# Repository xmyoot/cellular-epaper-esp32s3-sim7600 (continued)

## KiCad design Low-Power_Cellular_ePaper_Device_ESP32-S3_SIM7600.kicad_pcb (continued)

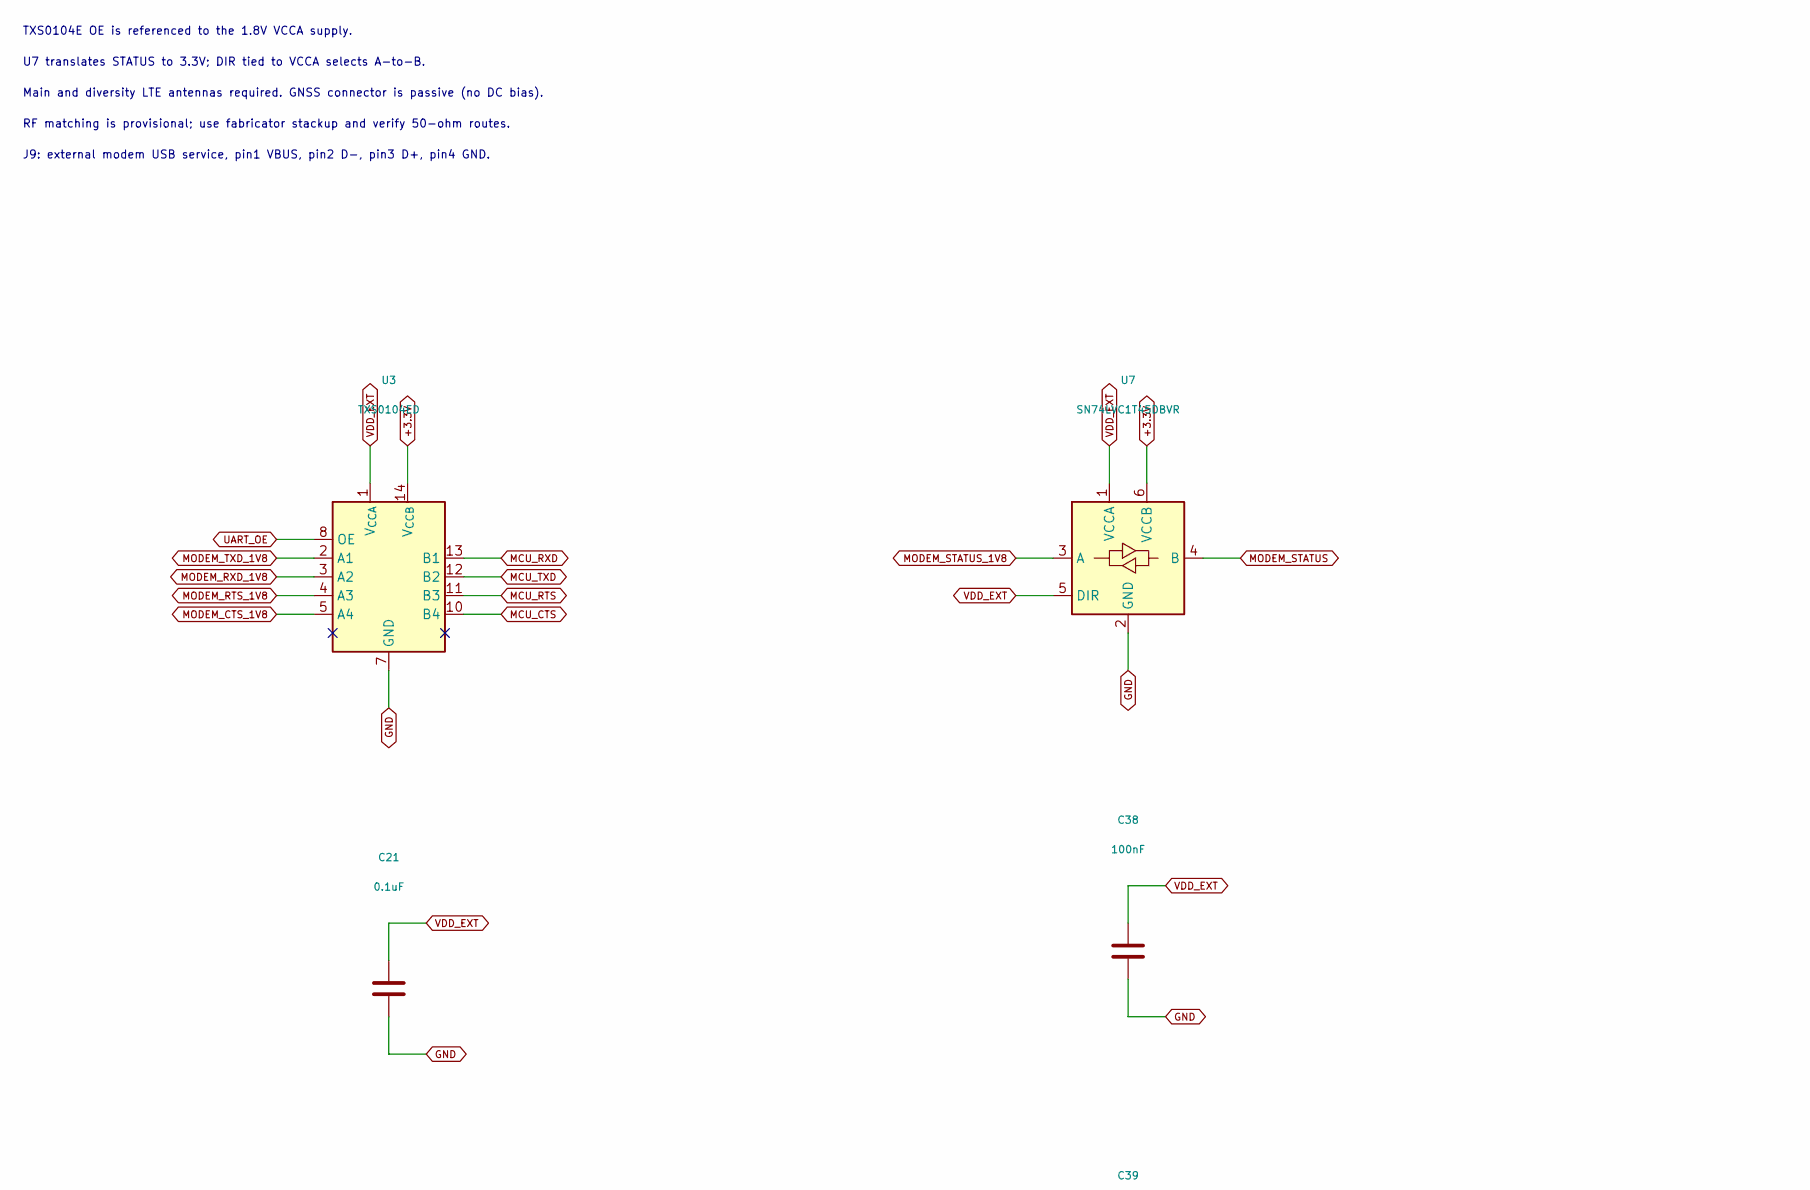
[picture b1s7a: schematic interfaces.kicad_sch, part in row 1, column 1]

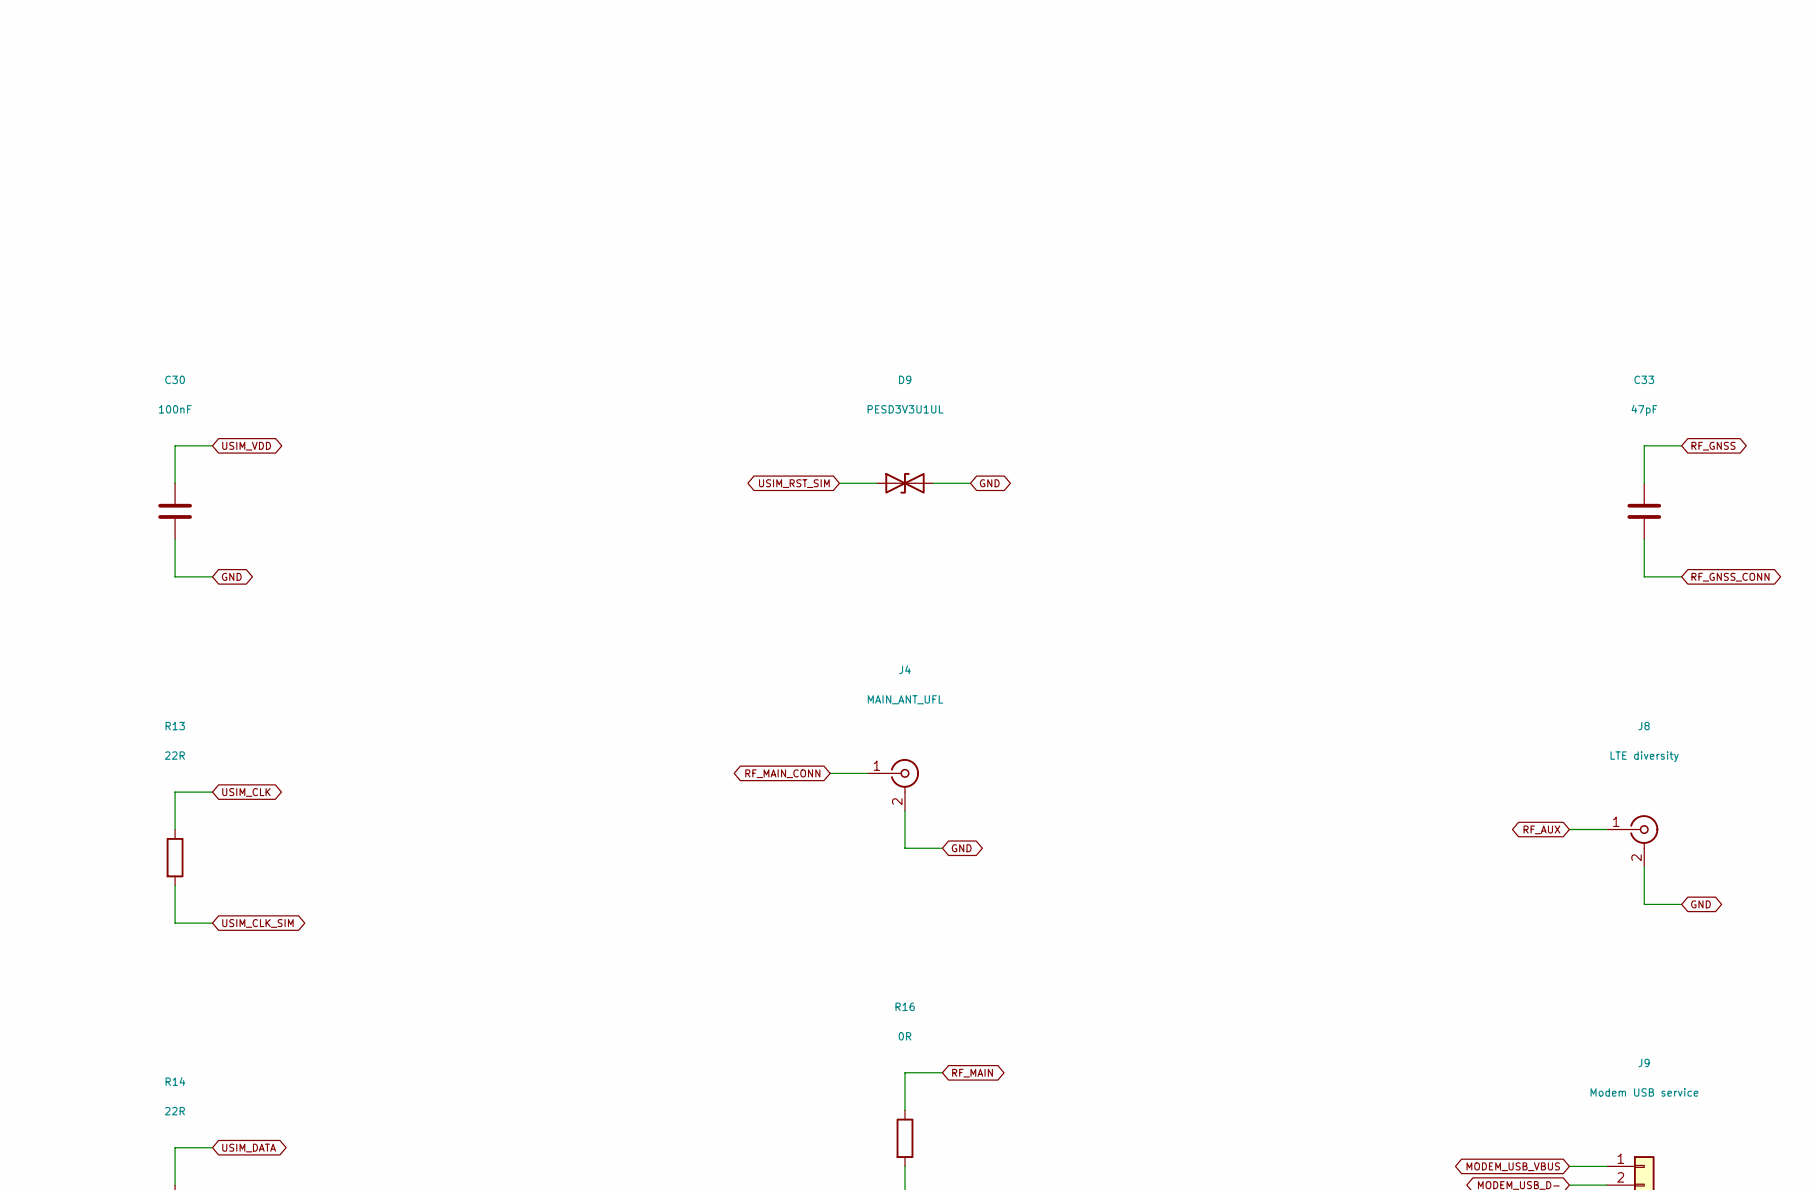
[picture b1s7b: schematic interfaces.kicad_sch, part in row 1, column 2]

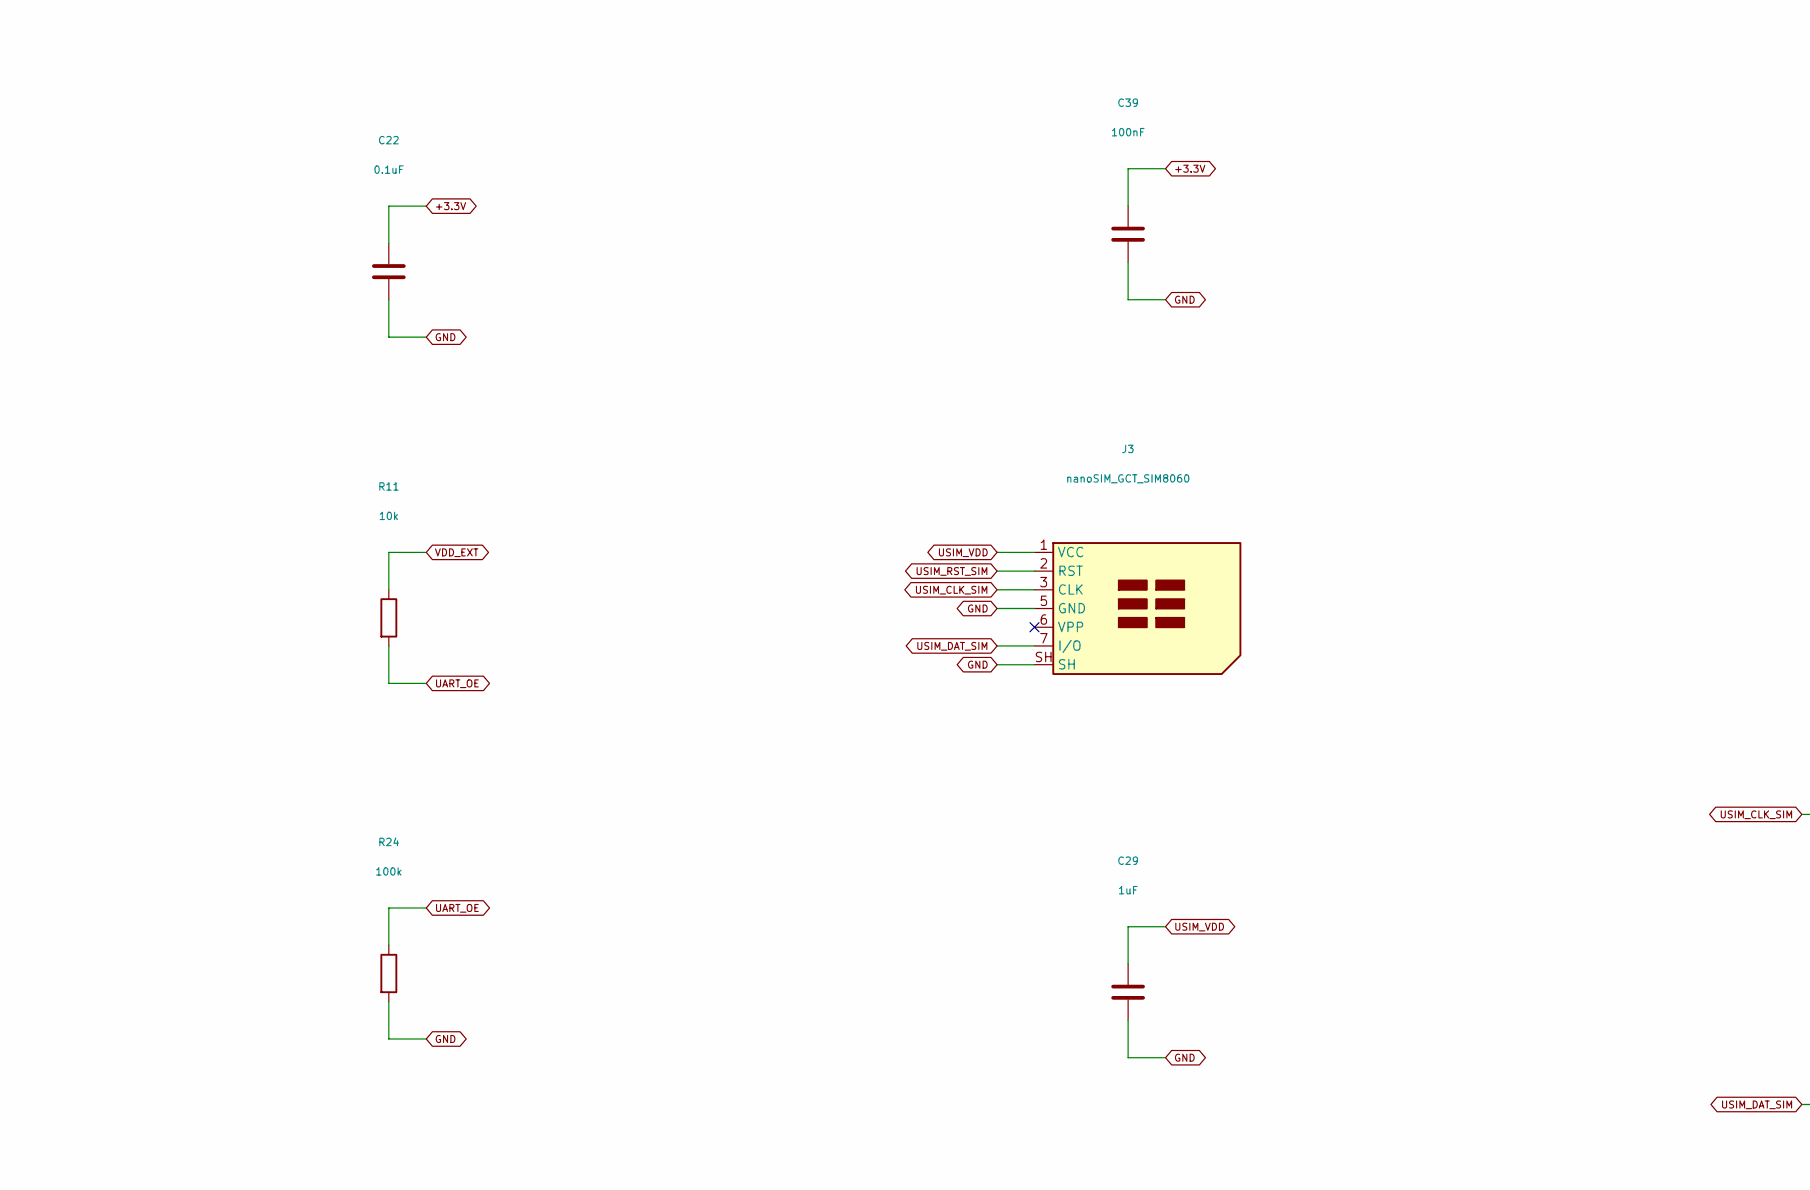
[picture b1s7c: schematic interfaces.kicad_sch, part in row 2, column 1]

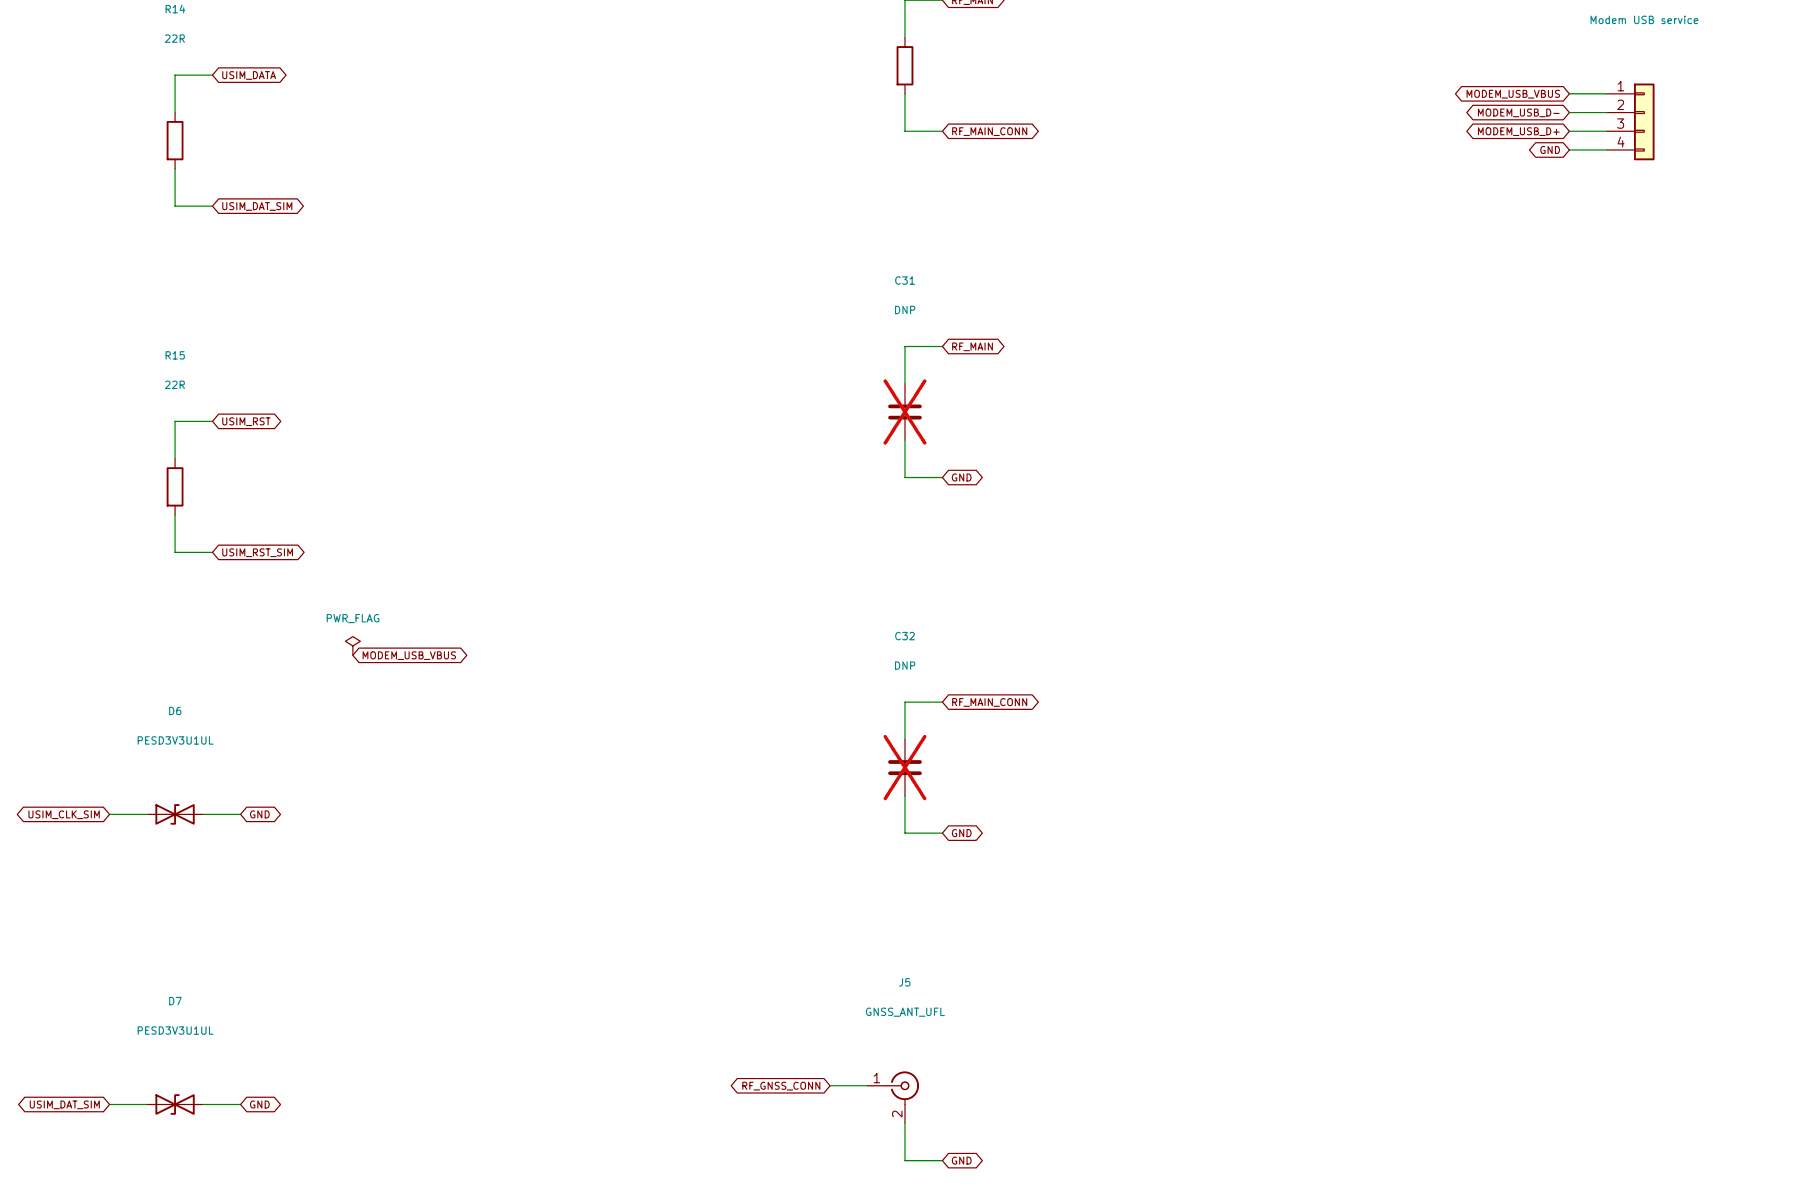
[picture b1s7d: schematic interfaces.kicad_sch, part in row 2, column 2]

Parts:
C21, C22: 0.1uF; C_0402_1005Metric
C29: 1uF; C_0603_1608Metric
C30: 100nF; C_0402_1005Metric
C31, C32: DNP; C_0402_1005Metric; not fitted
C33: 47pF; C_0402_1005Metric
C38, C39: 100nF; C_0603_1608Metric
D6, D9: PESD3V3U1UL; D_SOD-882
D7: PESD3V3U1UL; D_SOD-882_SIM
J3: nanoSIM_GCT_SIM8060; nanoSIM_GCT_SIM8060-6-0-14-00
J4: MAIN_ANT_UFL; U.FL_Hirose_U.FL-R-SMT-1_Vertical
J5: GNSS_ANT_UFL; U.FL_Hirose_U.FL-R-SMT-1_Vertical
J8: LTE diversity; U.FL_Hirose_U.FL-R-SMT-1_Vertical
J9: Modem USB service; PinHeader_1x04_P2.54mm_Vertical
R11: 10k; R_0603_1608Metric
R13, R14, R15: 22R; R_0402_1005Metric
R16: 0R; R_0402_1005Metric
R24: 100k; R_0603_1608Metric
U3: TXS0104ED; SOIC-14_3.9x8.7mm_P1.27mm
U7: SN74LVC1T45DBVR; SOT-23-6

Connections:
+3.3V: C22.1, C39.1, U3.14 (V_{CCB}), U7.6 (VCCB); also elsewhere on the board
GND: C21.2, C22.2, C29.2, C30.2, C31.2, C32.2, C38.2, C39.2, D6.2 (A2), D7.2 (A2), D9.2 (A2), J3.5 (GND), J3.SH, J4.2 (Ext), J5.2 (Ext), J8.2 (Ext), J9.4, R24.2, U3.7 (GND), U7.2 (GND); also elsewhere on the board
MCU_CTS: U3.10 (B4); also elsewhere on the board
MCU_RTS: U3.11 (B3); also elsewhere on the board
MCU_RXD: U3.13 (B1); also elsewhere on the board
MCU_TXD: U3.12 (B2); also elsewhere on the board
MODEM_CTS_1V8: U3.5 (A4); also elsewhere on the board
MODEM_RTS_1V8: U3.4 (A3); also elsewhere on the board
MODEM_RXD_1V8: U3.3 (A2); also elsewhere on the board
MODEM_STATUS: U7.4 (B); also elsewhere on the board
MODEM_STATUS_1V8: U7.3 (A); also elsewhere on the board
MODEM_TXD_1V8: U3.2 (A1); also elsewhere on the board
MODEM_USB_D+: J9.3; also elsewhere on the board
MODEM_USB_D-: J9.2; also elsewhere on the board
MODEM_USB_VBUS: J9.1; also elsewhere on the board
RF_AUX: J8.1 (In); also elsewhere on the board
RF_GNSS: C33.1; also elsewhere on the board
RF_GNSS_CONN: C33.2, J5.1 (In)
RF_MAIN: C31.1, R16.1; also elsewhere on the board
RF_MAIN_CONN: C32.1, J4.1 (In), R16.2
UART_OE: R11.2, R24.1, U3.8 (OE)
USIM_CLK: R13.1; also elsewhere on the board
USIM_CLK_SIM: D6.1 (A1), J3.3 (CLK), R13.2
USIM_DATA: R14.1; also elsewhere on the board
USIM_DAT_SIM: D7.1 (A1), J3.7 (I/O), R14.2
USIM_RST: R15.1; also elsewhere on the board
USIM_RST_SIM: D9.1 (A1), J3.2 (RST), R15.2
USIM_VDD: C29.1, C30.1, J3.1 (VCC); also elsewhere on the board
VDD_EXT: C21.1, C38.1, R11.1, U3.1 (V_{CCA}), U7.1 (VCCA), U7.5 (DIR); also elsewhere on the board

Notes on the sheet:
U7 translates STATUS to 3.3V; DIR tied to VCCA selects A-to-B.
J9: external modem USB service, pin1 VBUS, pin2 D-, pin3 D+, pin4 GND.
Main and diversity LTE antennas required. GNSS connector is passive (no DC bias).
TXS0104E OE is referenced to the 1.8V VCCA supply.
RF matching is provisional; use fabricator stackup and verify 50-ohm routes.

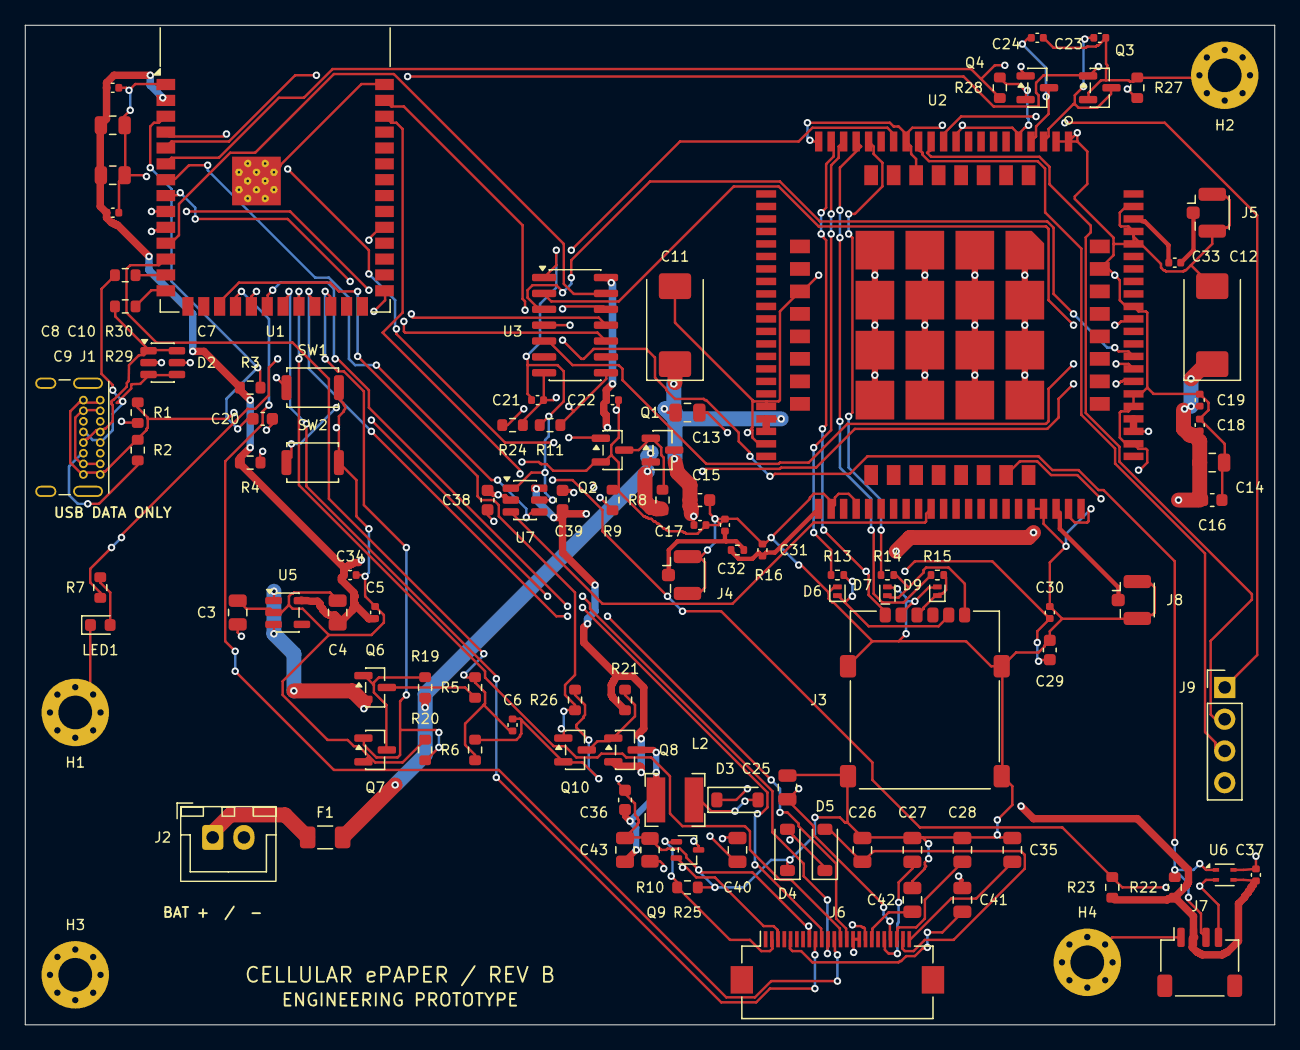
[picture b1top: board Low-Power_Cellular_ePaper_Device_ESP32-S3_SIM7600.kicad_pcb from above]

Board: 4 copper layers, 100.0 x 80.0 mm, 108 parts (0 on the bottom side), 75 nets.

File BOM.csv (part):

Reference,Value,Footprint,Assembly,Qualification
C10,0.1uF,Capacitor_SMD:C_0402_1005Metric,FIT,Engineering selection; validate ratings and procurement before fabrication
C11,220uF 6.3V T520D227M006ATE015,Capacitor_Tantalum_SMD:CP_EIA-7343-31_Kemet-D,FIT,Engineering selection; validate ratings and procurement before fabrication
C12,220uF 6.3V T520D227M006ATE015,Capacitor_Tantalum_SMD:CP_EIA-7343-31_Kemet-D,FIT,Engineering selection; validate ratings and procurement before fabrication
C13,47uF 10V,Capacitor_SMD:C_0805_2012Metric,FIT,Engineering selection; validate ratings and procurement before fabrication
C14,47uF 10V,Capacitor_SMD:C_0805_2012Metric,FIT,Engineering selection; validate ratings and procurement before fabrication
C15,10uF,Capacitor_SMD:C_0603_1608Metric,FIT,Engineering selection; validate ratings and procurement before fabrication
C16,10uF,Capacitor_SMD:C_0603_1608Metric,FIT,Engineering selection; validate ratings and procurement before fabrication
C17,0.1uF,Capacitor_SMD:C_0402_1005Metric,FIT,Engineering selection; validate ratings and procurement before fabrication
C18,0.1uF,Capacitor_SMD:C_0402_1005Metric,FIT,Engineering selection; validate ratings and procurement before fabrication
C19,33pF,Capacitor_SMD:C_0402_1005Metric,FIT,Engineering selection; validate ratings and procurement before fabrication
C20,1uF,Capacitor_SMD:C_0603_1608Metric,FIT,Engineering selection; validate ratings and procurement before fabrication
C21,0.1uF,Capacitor_SMD:C_0402_1005Metric,FIT,Engineering selection; validate ratings and procurement before fabrication
C22,0.1uF,Capacitor_SMD:C_0402_1005Metric,FIT,Engineering selection; validate ratings and procurement before fabrication
C23,100nF,Capacitor_SMD:C_0402_1005Metric,FIT,Engineering selection; validate ratings and procurement before fabrication
C24,100nF,Capacitor_SMD:C_0402_1005Metric,FIT,Engineering selection; validate ratings and procurement before fabrication
C25,1uF 25V,Capacitor_SMD:C_0805_2012Metric,FIT,Engineering selection; validate ratings and procurement before fabrication
C26,1uF 25V,Capacitor_SMD:C_0805_2012Metric,FIT,Engineering selection; validate ratings and procurement before fabrication
C27,1uF 25V,Capacitor_SMD:C_0805_2012Metric,FIT,Engineering selection; validate ratings and procurement before fabrication
C28,1uF 25V,Capacitor_SMD:C_0805_2012Metric,FIT,Engineering selection; validate ratings and procurement before fabrication
C29,1uF,Capacitor_SMD:C_0603_1608Metric,FIT,Engineering selection; validate ratings and procurement before fabrication
C3,10uF,Capacitor_SMD:C_0805_2012Metric,FIT,Engineering selection; validate ratings and procurement before fabrication
C30,100nF,Capacitor_SMD:C_0402_1005Metric,FIT,Engineering selection; validate ratings and procurement before fabrication
C31,DNP,Capacitor_SMD:C_0402_1005Metric,DNP,Engineering selection; validate ratings and procurement before fabrication
C32,DNP,Capacitor_SMD:C_0402_1005Metric,DNP,Engineering selection; validate ratings and procurement before fabrication
C33,47pF,Capacitor_SMD:C_0402_1005Metric,FIT,Engineering selection; validate ratings and procurement before fabrication
C34,100nF,Capacitor_SMD:C_0402_1005Metric,FIT,Engineering selection; validate ratings and procurement before fabrication
C35,1uF 25V,Capacitor_SMD:C_0805_2012Metric,FIT,Engineering selection; validate ratings and procurement before fabrication
C36,1uF 25V,Capacitor_SMD:C_0603_1608Metric,FIT,Engineering selection; validate ratings and procurement before fabrication
C37,0.1uF,Capacitor_SMD:C_0402_1005Metric,FIT,Engineering selection; validate ratings and procurement before fabrication
C38,100nF,Capacitor_SMD:C_0603_1608Metric,FIT,Engineering selection; validate ratings and procurement before fabrication
C39,100nF,Capacitor_SMD:C_0603_1608Metric,FIT,Engineering selection; validate ratings and procurement before fabrication
C4,10uF,Capacitor_SMD:C_0805_2012Metric,FIT,Engineering selection; validate ratings and procurement before fabrication
C40,4.7uF 25V,Capacitor_SMD:C_0805_2012Metric,FIT,Engineering selection; validate ratings and procurement before fabrication
C41,1uF 25V,Capacitor_SMD:C_0805_2012Metric,FIT,Engineering selection; validate ratings and procurement before fabrication
C42,1uF 25V,Capacitor_SMD:C_0805_2012Metric,FIT,Engineering selection; validate ratings and procurement before fabrication
C43,4.7uF 25V,Capacitor_SMD:C_0805_2012Metric,FIT,Engineering selection; validate ratings and procurement before fabrication
C5,0.1uF,Capacitor_SMD:C_0402_1005Metric,FIT,Engineering selection; validate ratings and procurement before fabrication
C6,100nF,Capacitor_SMD:C_0402_1005Metric,FIT,Engineering selection; validate ratings and procurement before fabrication
C7,10uF,Capacitor_SMD:C_0805_2012Metric,FIT,Engineering selection; validate ratings and procurement before fabrication
C8,10uF,Capacitor_SMD:C_0805_2012Metric,FIT,Engineering selection; validate ratings and procurement before fabrication
C9,0.1uF,Capacitor_SMD:C_0402_1005Metric,FIT,Engineering selection; validate ratings and procurement before fabrication
D2,USBLC6-2SC6,Package_TO_SOT_SMD:SOT-23-6,FIT,Engineering selection; validate ratings and procurement before fabrication
D3,MBR0530,Diode_SMD:D_SOD-123,FIT,Engineering selection; validate ratings and procurement before fabrication
D4,MBR0530,Diode_SMD:D_SOD-123,FIT,Engineering selection; validate ratings and procurement before fabrication
D5,MBR0530,Diode_SMD:D_SOD-123,FIT,Engineering selection; validate ratings and procurement before fabrication
D6,PESD3V3U1UL,Diode_SMD:D_SOD-882,FIT,Engineering selection; validate ratings and procurement before fabrication
D7,PESD3V3U1UL,Cellular:D_SOD-882_SIM,FIT,Engineering selection; validate ratings and procurement before fabrication
D9,PESD3V3U1UL,Diode_SMD:D_SOD-882,FIT,Engineering selection; validate ratings and procurement before fabrication
F1,2.5A fast fuse,Fuse:Fuse_1206_3216Metric,FIT,Engineering selection; validate ratings and procurement before fabrication
H1,M2.5,MountingHole:MountingHole_2.7mm_M2.5_Pad_Via,FIT,Engineering selection; validate ratings and procurement before fabrication
H2,M2.5,MountingHole:MountingHole_2.7mm_M2.5_Pad_Via,FIT,Engineering selection; validate ratings and procurement before fabrication
H3,M2.5,MountingHole:MountingHole_2.7mm_M2.5_Pad_Via,FIT,Engineering selection; validate ratings and procurement before fabrication
H4,M2.5,MountingHole:MountingHole_2.7mm_M2.5_Pad_Via,FIT,Engineering selection; validate ratings and procurement before fabrication
J1,USB-C,Cellular:USB4085_Edge,FIT,Engineering selection; validate ratings and procurement before fabrication
J2,Protected LiPo 3A,Connector_JST:JST_XH_B2B-XH-A_1x02_P2.50mm_Vertical,FIT,Engineering selection; validate ratings and procurement before fabrication
J3,nanoSIM_GCT_SIM8060,Connector_Card:nanoSIM_GCT_SIM8060-6-0-14-00,FIT,Engineering selection; validate ratings and procurement before fabrication
J4,MAIN_ANT_UFL,Connector_Coaxial:U.FL_Hirose_U.FL-R-SMT-1_Vertical,FIT,Engineering selection; validate ratings and procurement before fabrication
J5,GNSS_ANT_UFL,Connector_Coaxial:U.FL_Hirose_U.FL-R-SMT-1_Vertical,FIT,Engineering selection; validate ratings and procurement before fabrication
J6,FH12-24S-0.5SH,Connector_FFC-FPC:Hirose_FH12-24S-0.5SH_1x24-1MP_P0.50mm_Horizontal,FIT,Engineering selection; validate ratings and procurement before fabrication
J7,Qwiic / STEMMA QT,Connector_JST:JST_SH_SM04B-SRSS-TB_1x04-1MP_P1.00mm_Horizontal,FIT,Engineering selection; validate ratings and procurement before fabrication
J8,LTE diversity,Connector_Coaxial:U.FL_Hirose_U.FL-R-SMT-1_Vertical,FIT,Engineering selection; validate ratings and procurement before fabrication
J9,Modem USB service,Connector_PinHeader_2.54mm:PinHeader_1x04_P2.54mm_Vertical,FIT,Engineering selection; validate ratings and procurement before fabrication
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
